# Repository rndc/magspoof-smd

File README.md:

### Magspoof SMD
---
Samy Kamkar's Magspoof using SMD components. You should check [his repository here](https://github.com/samyk/magspoof).
This repository only contains the modified schematic and board layout without source for the firmware.

### Disclaimer
---
For educational purpose ONLY. Use at your own risk.

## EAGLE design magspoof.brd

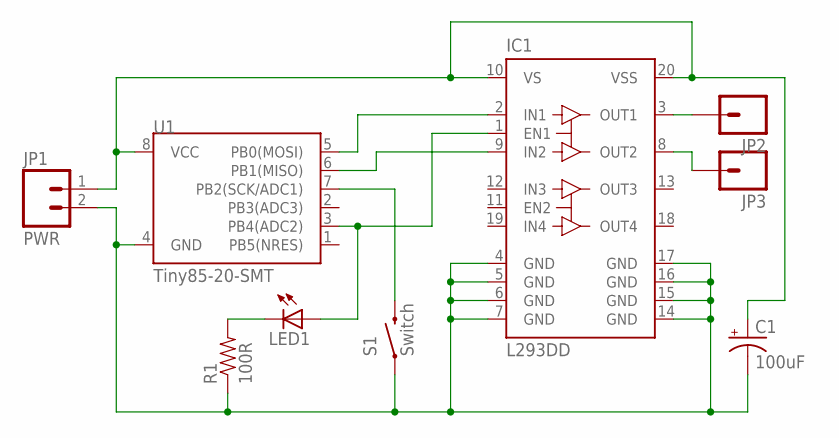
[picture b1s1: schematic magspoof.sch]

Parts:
C1: 100uF; NIC_10X10.5_CAP
IC1: L293DD; SO20
JP1: PWR; JST-2-SMD
JP2, JP3: M01SMDNS; 1X01NS
LED1: LEDCHIP-LED0805; CHIP-LED0805
R1: 100R; 0603-RES
S1: Switch; TACTILE-SWITCH-SMD
U1: Tiny85-20-SMT; SO08-EIAJ

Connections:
unnamed: C1.+, IC1.10 (VS), IC1.20 (VSS), JP1.1 (2), U1.8 (VCC)
unnamed: C1.-, IC1.4 (GND), IC1.5 (GND), IC1.6 (GND), IC1.7 (GND), IC1.14 (GND), IC1.15 (GND), IC1.16 (GND), IC1.17 (GND), JP1.2 (1), R1.1, S1.1, S1.2 (1), U1.4 (GND)
unnamed: LED1.C, R1.2
unnamed: S1.3 (2), S1.4 (2), U1.7 (PB2(SCK/ADC1))
unnamed: IC1.1 (EN1), LED1.A, U1.3 (PB4(ADC2))
unnamed: IC1.3 (OUT1), JP2.1
unnamed: IC1.8 (OUT2), JP3.1
unnamed: IC1.2 (IN1), U1.5 (PB0(MOSI))
unnamed: IC1.9 (IN2), U1.6 (PB1(MISO))

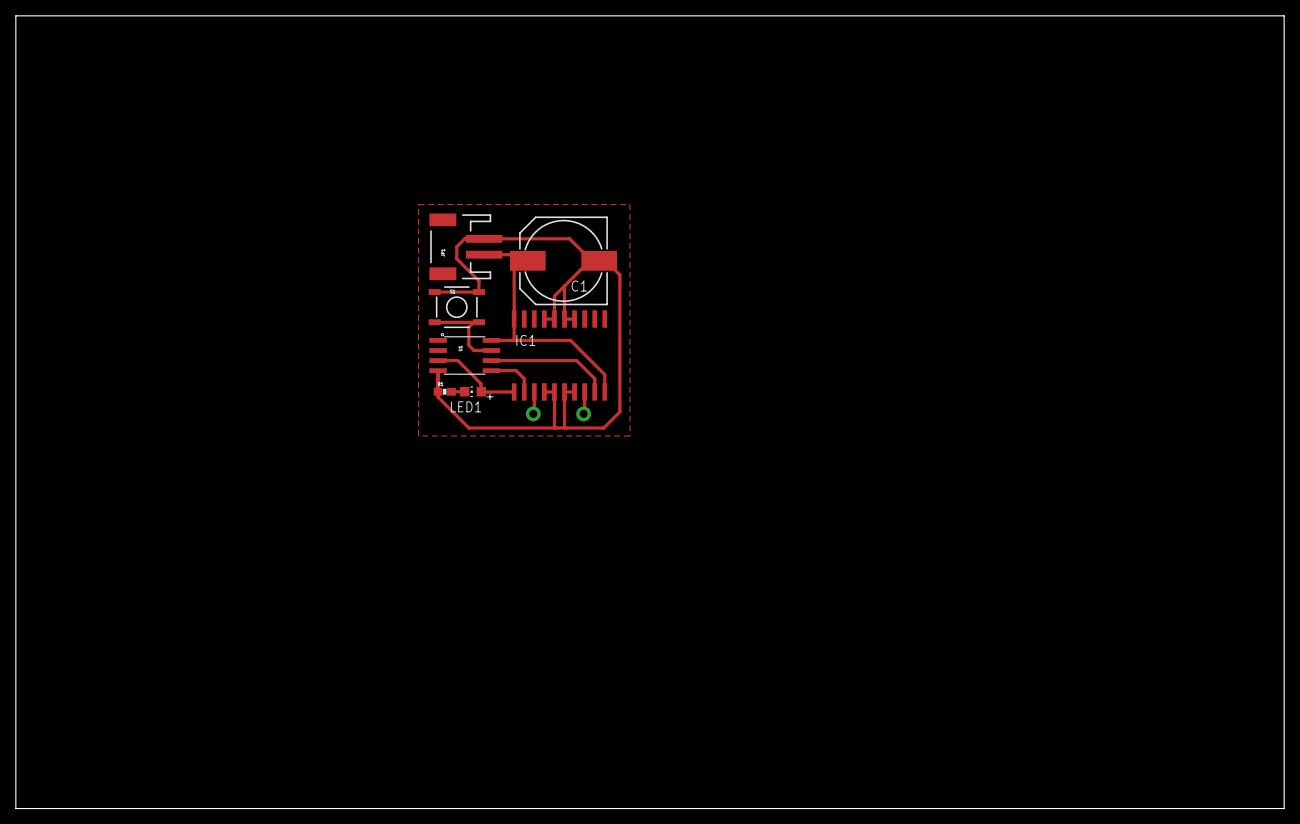
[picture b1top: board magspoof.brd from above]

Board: 2 copper layers, 160.0 x 100.0 mm, 9 parts (0 on the bottom side), 9 nets.

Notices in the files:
parts and their libraries:
SparkFun-Capacitors: Licensing: Creative Commons ShareAlike 4.0 International - https://creativecommons.org/licenses/by-sa/4.0
